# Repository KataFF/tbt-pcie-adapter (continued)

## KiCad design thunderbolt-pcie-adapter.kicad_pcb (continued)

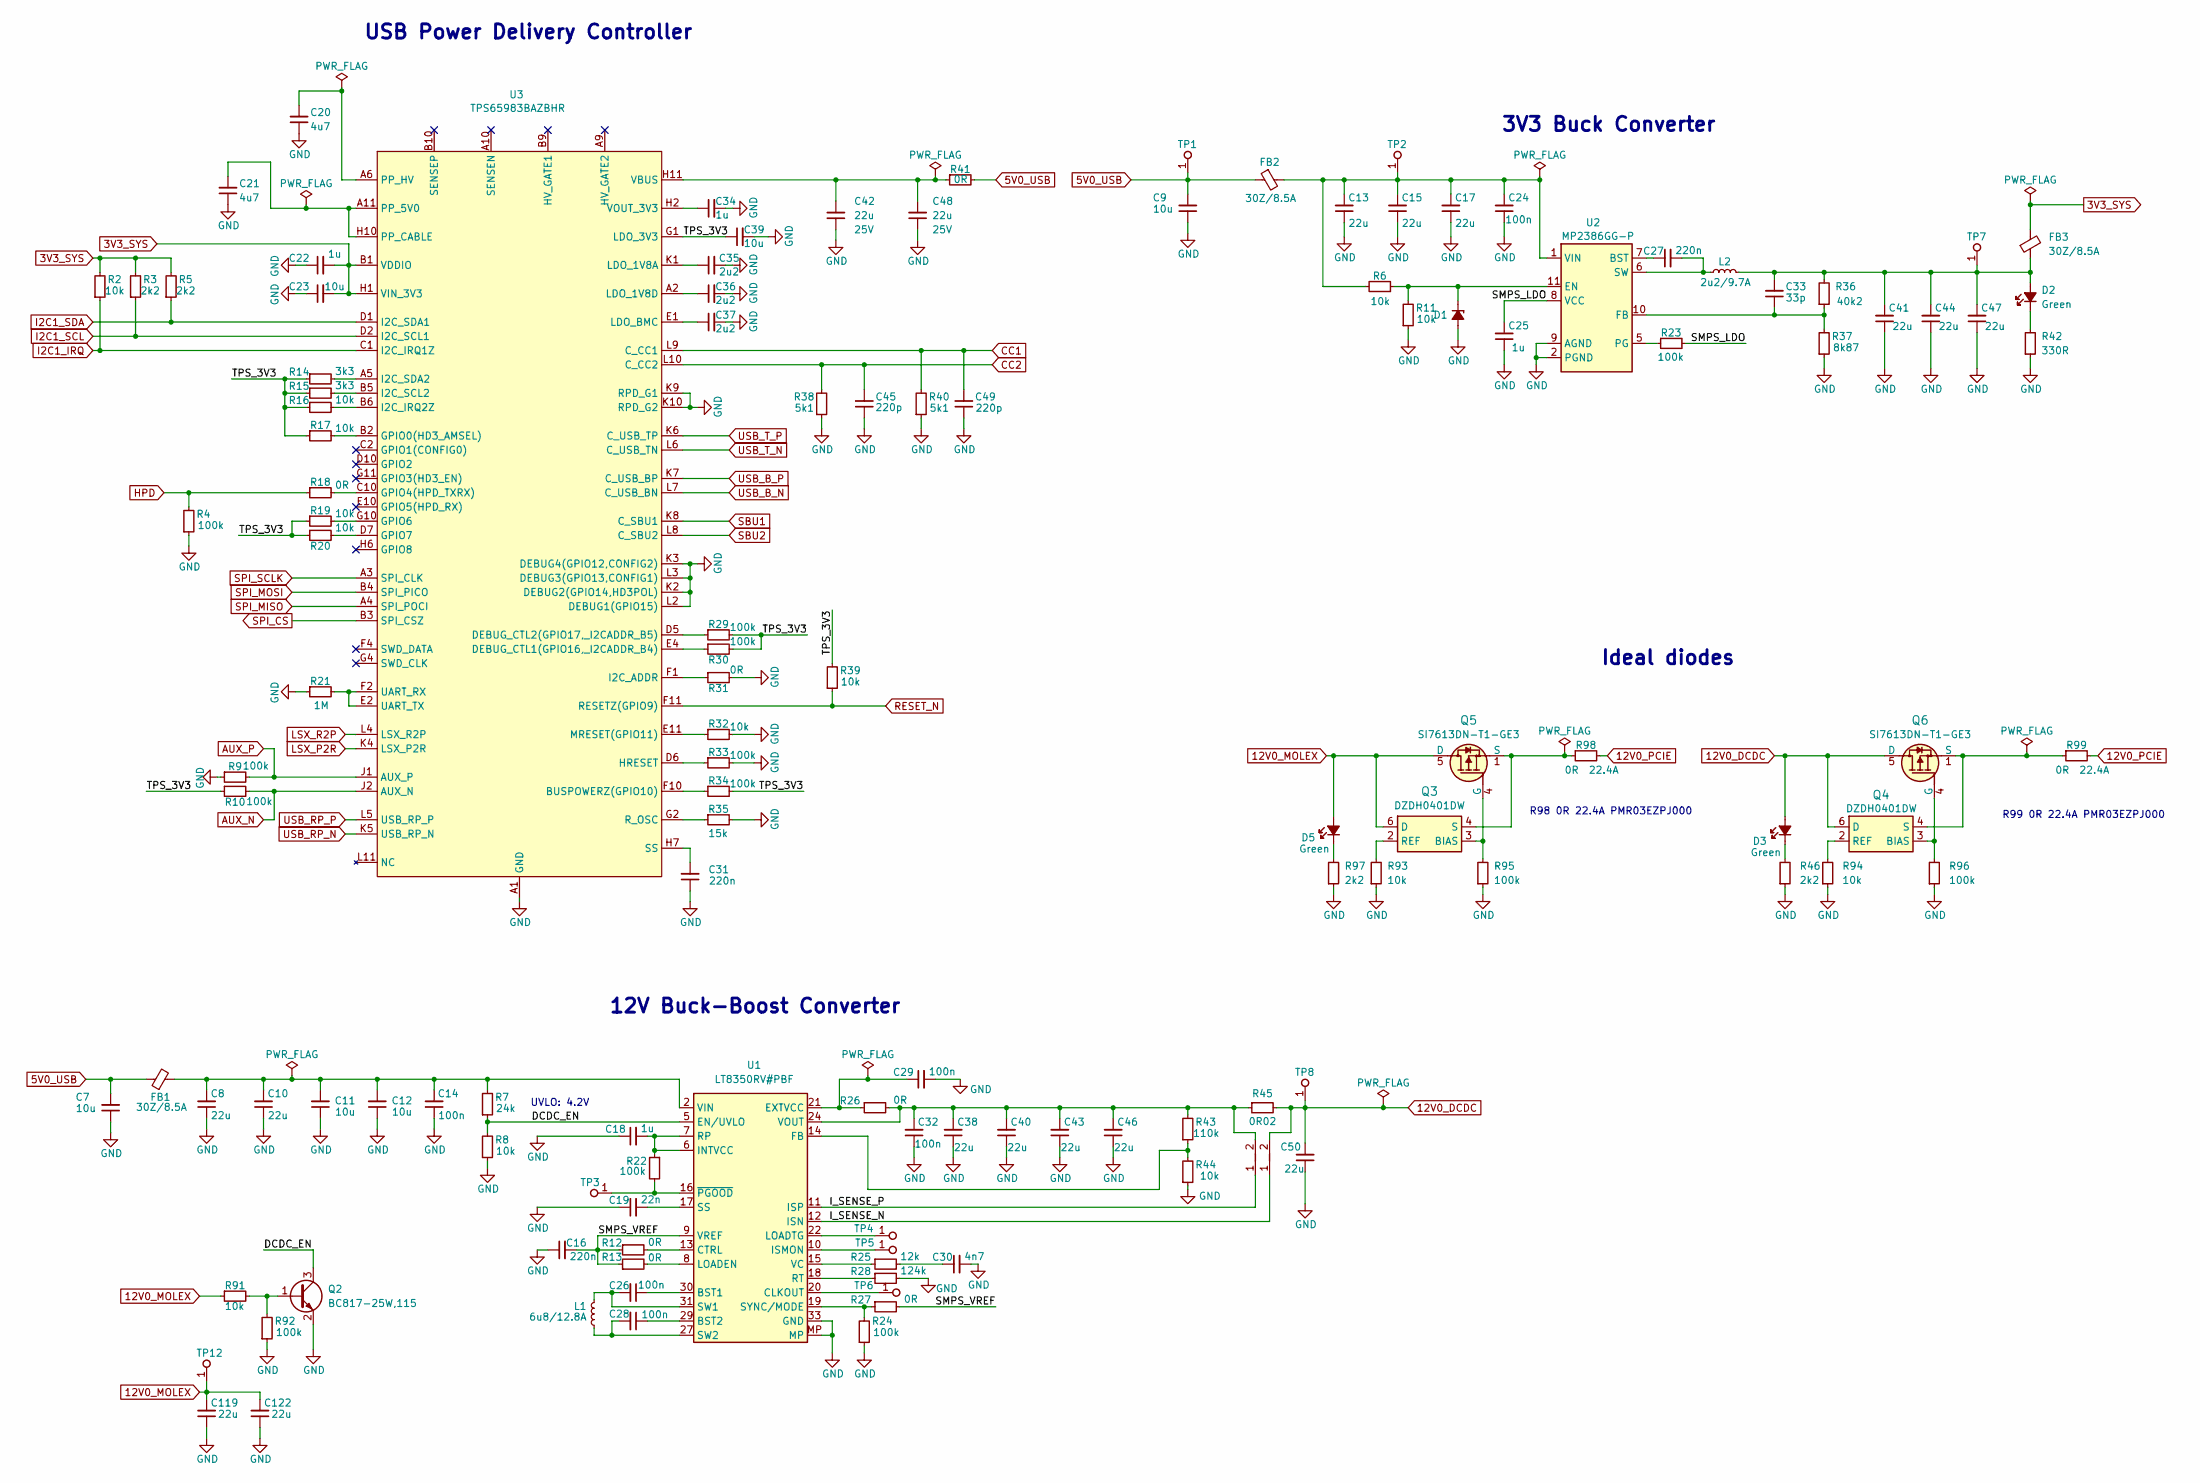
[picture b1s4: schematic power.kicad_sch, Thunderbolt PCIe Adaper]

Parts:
C7, C9, C11, C12: C_10u_0805_35V; C_0805_2012Metric; Voltage 35V; MPN GRM21BR6YA106KE43L
C8, C10, C13, C15, C17: C_22u_1206_35V; C_1206_3216Metric; Voltage 35V; MPN 3216X5R1V226M160AC
C14, C24, C26, C28, C29, C32: C_100n_0402; C_0402_1005Metric; Voltage 50V; MPN GRM155R61H104KE14D
C16, C27, C31: C_220n_0402; C_0402_1005Metric; MPN CC0402KRX5R6BB224
C18, C22, C25, C34: C_1u_0402; C_0402_1005Metric; MPN C1005X6S1A105K050BC
C19: C_22n_0402; C_0402_1005Metric; MPN GCM155R71H223MA55D
C20, C21: C_4u7_25V_0402; C_0402_1005Metric; Voltage 25V; MPN GRM155C61E475ME15J
C23, C39: C_10u_0402; C_0402_1005Metric; MPN CC0402MRX5R5BB106
C30: C_4n7_0402; C_0402_1005Metric; MPN CGA2B3X7S2A472K050BB
C33: C_33p_0402; C_0402_1005Metric; MPN 04025A330FAT2A
C35, C36, C37: C_2u2_0402; C_0402_1005Metric; MPN C1005X5R1A225K050BC
C38, C40, C43, C46, C50, C119, C122: C_22u_16V_0603; C_0603_1608Metric; Voltage 16V; MPN CL10A226MO7JZNC
C41, C44, C47: C_22u_0603; C_0603_1608Metric; MPN GRM188R60J226MEA0D
C42, C48: C_22u_25V_0805; C_0805_2012Metric; Voltage 25V; MPN CL21A226MAYNNNE
C45, C49: C_220p_0402; C_0402_1005Metric; MPN 04025C221JAT2A
D1: MM3Z3V3C; D_SOD-323F; MPN MM3Z3V3C
D2, D3, D5: LED_G_0603_KP-1608CGCK; LED_0603_1608Metric_G; MPN KP-1608CGCK
FB1, FB2, FB3: FB_30Z_8.5A_Murata-BLM21SN_0805; FB_0805_2012Metric; MPN BLM21SN300SZ1D
L1: L_6u8_12.8A_Coilcraft-XAL7070; L_Coilcraft-XAL7070; MPN XAL7070-682MEC
L2: L_2u2_9.7A_Coilcraft-XAL5030; L_Coilcraft-XAL5030; MPN XAL5030-222MEC
Q2: BC817-25W; SOT-323; MPN BC817-25W,115
Q3, Q4: DZDH0401DW; SOT-363; MPN DZDH0401DW
Q5, Q6: SI7613DN-T1-GE3; Vishay_PowerPAK_1212-8_Single; MPN SI7613DN-T1-GE3
R2, R6, R8, R11, R16, R17, R19, R20, R32, R39, R44, R91, R93, R94: R_10k_0402; R_0402_1005Metric; Tolerance 1%; MPN CR0402-FX-1002GLF
R3, R5, R46, R97: R_2k2_0402; R_0402_1005Metric; Tolerance 1%; MPN CR0402-FX-2201GLF
R4, R9, R10, R22, R23, R24, R29, R30, R33, R34, R92, R95, R96: R_100k_0402; R_0402_1005Metric; Tolerance 1%; MPN CR0402-FX-1003GLF
R7: R_24k_0402; R_0402_1005Metric; Tolerance 1%; MPN CR0402-FX-2402GLF
R12, R13, R18, R26, R27, R31: R_0R_0402; R_0402_1005Metric; MPN ERJ2GE0R00X
R14, R15: R_3k3_0402; R_0402_1005Metric; Tolerance 1%; MPN CR0402-FX-3301GLF
R21: R_1M_0402; R_0402_1005Metric; Tolerance 1%; MPN CR0402-FX-1004GLF
R25: R_12k_0402; R_0402_1005Metric; Tolerance 1%; MPN CR0402-FX-1202GLF
R28: R_124k_0402; R_0402_1005Metric; Tolerance 1%; MPN CR0402-FX-1243GLF
R35: R_15k_0.1%_0402; R_0402_1005Metric; Tolerance 0.1%; MPN ERA-2ARB153X
R36: R_40k2_0402; R_0402_1005Metric; Tolerance 1%; MPN CR0402-FX-4022GLF
R37: R_8k87_0402; R_0402_1005Metric; Tolerance 1%; MPN CR0402-FX-8871GLF
R38, R40: R_5k1_0402; R_0402_1005Metric; Tolerance 1%; MPN CR0402-FX-5101GLF
R41: R_0R_0603; R_0603_1608Metric; MPN CR0603-J/-000ELF
R42: R_330R_0402; R_0402_1005Metric; Tolerance 1%; MPN CR0402-FX-3300GLF
R43: R_110k_0402; R_0402_1005Metric; Tolerance 1%; MPN CR0402-FX-1103GLF
R45: R_0R02_1206; R_1206_3216Metric; Tolerance 1%; MPN WSLP1206R0200FEA
R98, R99: R_0R_22.4A_0603; R_0603_1608Metric; Tolerance template_tolerance; MPN PMR03EZPJ000
TP1, TP2, TP3, TP5, TP7, TP8, TP12: TP_1mm_SMD; TP_SMD_1mm
TP4, TP6: TP_0.75mm_SMD; TP_SMD_0.75mm
TP10, TP11: Net-Tie_P0.1mm; NetTie-2_SMD_Pad0.1mm
U1: LT8350RV; QFN-32-4EP_4x6mm_P0.5mm; MPN LT8350RV#PBF
U2: MP2386GG; QFN-11_2x2mm_P0.5mm; MPN MP2386GG-P
U3: TPS65983BAZBHR; IC_TPS65983BAZBHR; MPN TPS65983BAZBHR

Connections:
3V3_SYS: C22.2, C23.2, FB3.2, R2.2, R3.2, R5.2, U3.B1 (VDDIO), U3.H1 (VIN_3V3); also elsewhere on the board
5V0_USB: C7.2, C9.2, FB1.1, FB2.1, R41.2, TP1.1; also elsewhere on the board
12V0_DCDC: C50.2, D3.2 (A), Q4.6 (D), Q6.5 (D), R45.2, TP8.1, TP11.2
12V0_MOLEX: C119.2, C122.2, D5.2 (A), Q3.6 (D), Q5.5 (D), R91.1, TP12.1; also elsewhere on the board
12V0_PCIE: R98.2, R99.2; also elsewhere on the board
/Power/DCDC_EN: Q2.3 (C), R7.1, R8.2, U1.5 (EN/UVLO)
/Power/I_SENSE_N: TP11.1, U1.12 (ISN)
/Power/I_SENSE_P: TP10.1, U1.11 (ISP)
/Power/SMPS_LDO: C25.2, R23.2, U2.8 (VCC)
/Power/SMPS_VREF: C16.2, R12.1, R13.1, R27.2, U1.9 (VREF)
/Power/TPS_3V3: C39.1, R10.1, R14.1, R15.1, R16.1, R17.1, R19.1, R20.1, R29.2, R30.2, R34.2, R39.2, U3.G1 (LDO_3V3)
AUX_N: R10.2, U3.J2 (AUX_N); also elsewhere on the board
AUX_P: R9.2, U3.J1 (AUX_P); also elsewhere on the board
CC1: C49.2, R40.2, U3.L9 (C_CC1); also elsewhere on the board
CC2: C45.2, R38.2, U3.L10 (C_CC2); also elsewhere on the board
GND: C7.1, C8.1, C9.1, C10.1, C11.1, C12.1, C13.1, C14.1, C15.1, C16.1, C17.1, C18.1, C19.1, C20.1, C21.1, C22.1, C23.1, C24.1, C25.1, C29.2, C30.2, C31.1, C32.1, C34.2, C35.2, C36.2, C37.2, C38.1, C39.2, C40.1, C41.1, C42.1, C43.1, C44.1, C45.1, C46.1, C47.1, C48.1, C49.1, C50.1, C119.1, C122.1, D1.2 (A), Q2.2 (E), R4.1, R8.1, R9.1, R11.1, R21.1, R24.1, R28.2, R31.2, R32.2, R33.2, R35.2, R37.1, R38.1, R40.1, R42.1, R44.1, R46.1, R92.1, R93.1, R94.1, R95.1, R96.1, R97.1, U1.33 (GND), U1.34 (GND), U1.35 (GND), U1.36 (GND), U1.MP, U2.2 (PGND), U2.3 (PGND), U2.4 (PGND), U2.9 (AGND), U3.A1 (GND), U3.B8 (GND), U3.D8 (GND), U3.E5 (GND), U3.E6 (GND), U3.E7 (GND), U3.E8 (GND), U3.F5 (GND), U3.F6 (GND), U3.F7 (GND), U3.F8 (GND), U3.G5 (GND), U3.G6 (GND), U3.G7 (GND), U3.G8 (GND), U3.H4 (GND), U3.H5 (GND), U3.H8 (GND), U3.K2 (DEBUG2(GPIO14,HD3POL)), U3.K3 (DEBUG4(GPIO12,CONFIG2)), U3.K9 (RPD_G1), U3.K10 (RPD_G2), U3.L1 (GND), U3.L2 (DEBUG1(GPIO15)), U3.L3 (DEBUG3(GPIO13,CONFIG1)); also elsewhere on the board
HPD: R4.2, R18.1; also elsewhere on the board
I2C1_IRQ: R2.1, U3.C1 (I2C_IRQ1Z); also elsewhere on the board
I2C1_SCL: R3.1, U3.D2 (I2C_SCL1); also elsewhere on the board
I2C1_SDA: R5.1, U3.D1 (I2C_SDA1); also elsewhere on the board
LSX_P2R: U3.K4 (LSX_P2R); also elsewhere on the board
LSX_R2P: U3.L4 (LSX_R2P); also elsewhere on the board
unnamed: C8.2, C10.2, C11.2, C12.2, C14.2, FB1.2, R7.2, U1.2 (VIN), U1.3 (VIN)
unnamed: C26.2, L1.1, U1.31 (SW1), U1.32 (SW1)
unnamed: C28.2, L1.2, U1.27 (SW2), U1.28 (SW2)
unnamed: C30.1, R25.2
unnamed: C32.2, C38.2, C40.2, C43.2, C46.2, R26.2, R43.2, R45.1, TP10.2, U1.24 (VOUT), U1.25 (VOUT)
unnamed: D1.1 (C), R6.1, R11.2, U2.11 (EN)
unnamed: C33.2, C41.2, C44.2, C47.2, D2.2 (A), FB3.1, L2.2, R36.2, TP7.1
unnamed: D2.1 (C), R42.2
unnamed: D3.1 (C), R46.2
unnamed: D5.1 (C), R97.2
unnamed: Q2.1 (B), R91.2, R92.2
unnamed: Q3.3 (BIAS), Q5.4 (G), R95.2
unnamed: Q3.2 (REF), R93.2
unnamed: Q3.4 (S), Q5.1 (S), Q5.2 (S), Q5.3 (S), R98.1
unnamed: Q4.3 (BIAS), Q6.4 (G), R96.2
unnamed: Q4.2 (REF), R94.2
unnamed: Q4.4 (S), Q6.1 (S), Q6.2 (S), Q6.3 (S), R99.1
unnamed: C26.1, U1.30 (BST1)
unnamed: C28.1, U1.29 (BST2)
unnamed: TP6.1, U1.20 (CLKOUT)
unnamed: R12.2, U1.13 (CTRL)
unnamed: C29.1, R26.1, U1.21 (EXTVCC)
unnamed: R43.1, R44.2, U1.14 (FB)
unnamed: C18.2, R22.1, U1.6 (INTVCC), U1.7 (RP)
unnamed: TP5.1, U1.10 (ISMON)
unnamed: R13.2, U1.8 (LOADEN)
unnamed: TP4.1, U1.22 (LOADTG)
unnamed: R28.1, U1.18 (RT)
unnamed: C19.2, U1.17 (SS)
unnamed: R24.2, R27.1, U1.19 (SYNC/MODE)
unnamed: R25.1, U1.15 (VC)
unnamed: R22.2, TP3.1, U1.16 (~PGOOD)
unnamed: C27.1, U2.7 (BST)
unnamed: C33.1, R36.1, R37.2, U2.10 (FB)
unnamed: R23.1, U2.5 (PG)
unnamed: C27.2, L2.1, U2.6 (SW)
unnamed: C13.2, C15.2, C17.2, C24.2, FB2.2, R6.2, TP2.1, U2.1 (VIN)
unnamed: R34.1, U3.F10 (BUSPOWERZ(GPIO10))
unnamed: R30.1, U3.E4 (DEBUG_CTL1(GPIO16,_I2CADDR_B4))
unnamed: R29.1, U3.D5 (DEBUG_CTL2(GPIO17,_I2CADDR_B5))
unnamed: R17.2, U3.B2 (GPIO0(HD3_AMSEL))
unnamed: R18.2, U3.C10 (GPIO4(HPD_TXRX))
unnamed: R19.2, U3.G10 (GPIO6)
unnamed: R20.2, U3.D7 (GPIO7)
unnamed: R33.1, U3.D6 (HRESET)
unnamed: R31.1, U3.F1 (I2C_ADDR)
unnamed: R16.2, U3.B6 (I2C_IRQ2Z)
unnamed: R15.2, U3.B5 (I2C_SCL2)
unnamed: R14.2, U3.A5 (I2C_SDA2)
unnamed: C35.1, U3.K1 (LDO_1V8A)
unnamed: C36.1, U3.A2 (LDO_1V8D)
unnamed: C37.1, U3.E1 (LDO_BMC)
unnamed: R32.1, U3.E11 (MRESET(GPIO11))
unnamed: R35.1, U3.G2 (R_OSC)
unnamed: C31.2, U3.H7 (SS)
unnamed: R21.2, U3.E2 (UART_TX), U3.F2 (UART_RX)
unnamed: C34.1, U3.H2 (VOUT_3V3)
PP_5V0: C21.2, U3.A11 (PP_5V0), U3.B11 (PP_5V0), U3.C11 (PP_5V0), U3.D11 (PP_5V0), U3.H10 (PP_CABLE)
PP_HV: C20.2, U3.A6 (PP_HV), U3.A7 (PP_HV), U3.A8 (PP_HV), U3.B7 (PP_HV)
RESET_N: R39.1, U3.F11 (RESETZ(GPIO9)); also elsewhere on the board
SBU1: U3.K8 (C_SBU1); also elsewhere on the board
SBU2: U3.L8 (C_SBU2); also elsewhere on the board
SPI_CS: U3.B3 (SPI_CSZ); also elsewhere on the board
SPI_MISO: U3.A4 (SPI_POCI); also elsewhere on the board
SPI_MOSI: U3.B4 (SPI_PICO); also elsewhere on the board
SPI_SCLK: U3.A3 (SPI_CLK); also elsewhere on the board
USB_B_N: U3.L7 (C_USB_BN); also elsewhere on the board
USB_B_P: U3.K7 (C_USB_BP); also elsewhere on the board
USB_RP_N: U3.K5 (USB_RP_N); also elsewhere on the board
USB_RP_P: U3.L5 (USB_RP_P); also elsewhere on the board
USB_T_N: U3.L6 (C_USB_TN); also elsewhere on the board
USB_T_P: U3.K6 (C_USB_TP); also elsewhere on the board
VBUS: C42.2, C48.2, R41.1, U3.H11 (VBUS), U3.J10 (VBUS), U3.J11 (VBUS), U3.K11 (VBUS)

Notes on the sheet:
UVLO: 4.2V
R99 0R 22.4A PMR03EZPJ000
Ideal diodes
USB Power Delivery Controller
12V Buck-Boost Converter
3V3 Buck Converter
R98 0R 22.4A PMR03EZPJ000

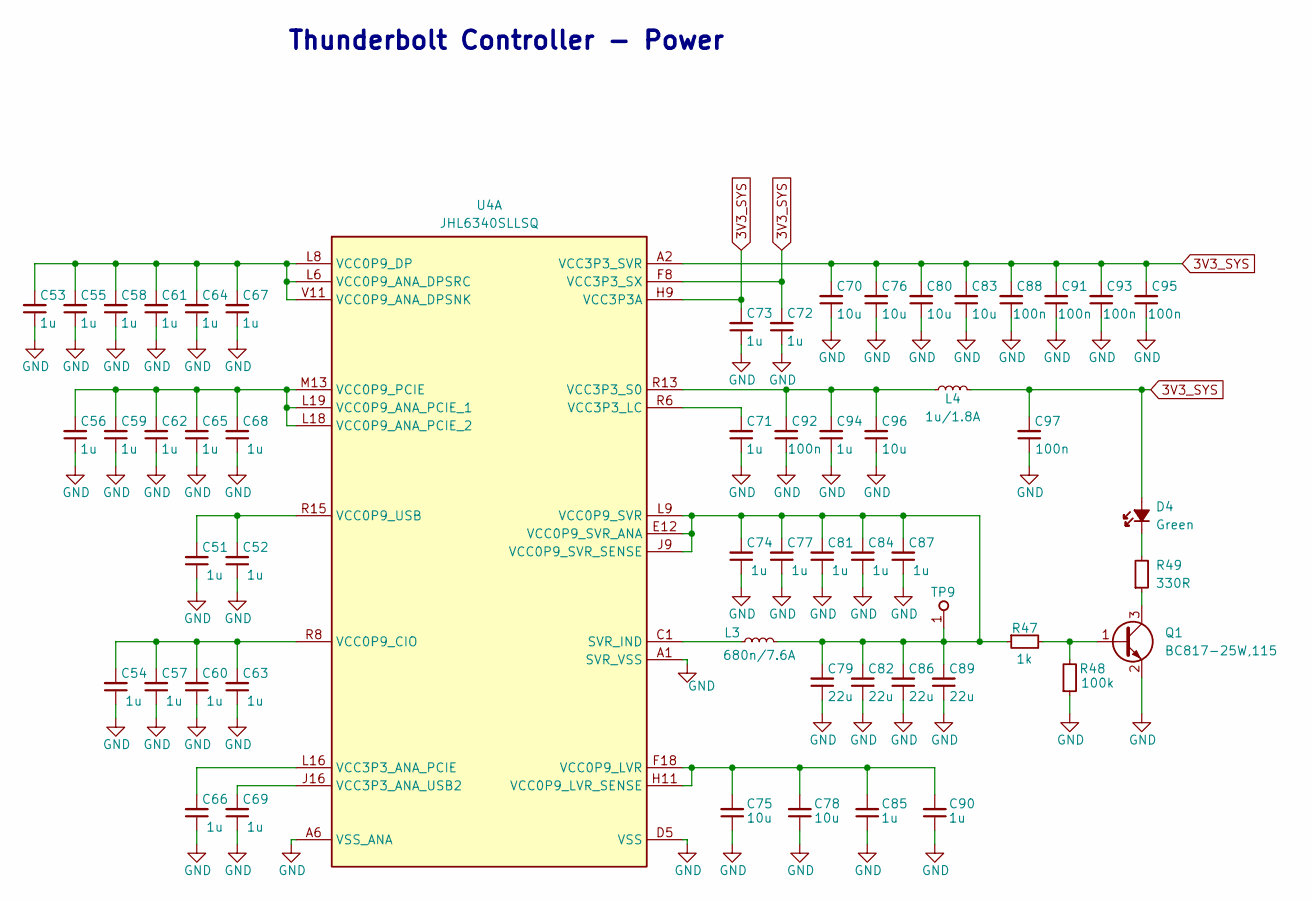
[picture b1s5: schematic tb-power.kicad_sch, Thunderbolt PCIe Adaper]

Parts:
C51, C52, C53, C54, C55, C56, C57, C58, C59, C60, C61, C62, C63, C64, C65, C66, C67, C68, C69, C71, C72, C73, C74, C77, C81, C84, C85, C87, C90, C94: C_1u_0402; C_0402_1005Metric; MPN C1005X6S1A105K050BC
C70, C75, C76, C78, C80, C83, C96: C_10u_0402; C_0402_1005Metric; MPN CC0402MRX5R5BB106
C79, C82, C86, C89: C_22u_0603; C_0603_1608Metric; MPN GRM188R60J226MEA0D
C88, C91, C92, C93, C95, C97: C_100n_0402; C_0402_1005Metric; Voltage 50V; MPN GRM155R61H104KE14D
D4: LED_G_0603_KP-1608CGCK; LED_0603_1608Metric_G; MPN KP-1608CGCK
L3: L_680n_7.6A_IHLP1616BZ; L_Vishay-IHLP1616BZ; MPN IHLP1616BZERR68M5A
L4: L_1u_1.8A_0603; L_0603_1608Metric; MPN DFE18SBN1R0ME0L
Q1: BC817-25W; SOT-323; MPN BC817-25W,115
R47: R_1k_0402; R_0402_1005Metric; Tolerance 1%; MPN CR0402-FX-1001GLF
R48: R_100k_0402; R_0402_1005Metric; Tolerance 1%; MPN CR0402-FX-1003GLF
R49: R_330R_0402; R_0402_1005Metric; Tolerance 1%; MPN CR0402-FX-3300GLF
TP9: TP_1mm_SMD; TP_SMD_1mm
U4: JHL6340SLLSQ; MPN JHL6340SLLSQ

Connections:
3V3_SYS: C70.2, C72.2, C73.2, C76.2, C80.2, C83.2, C88.2, C91.2, C93.2, C95.2, C97.2, D4.2 (A), L4.2, U4.A2 (VCC3P3_SVR), U4.A3 (VCC3P3_SVR), U4.B3 (VCC3P3_SVR), U4.F8 (VCC3P3_SX), U4.H9 (VCC3P3A); also elsewhere on the board
GND: C51.1, C52.1, C53.1, C54.1, C55.1, C56.1, C57.1, C58.1, C59.1, C60.1, C61.1, C62.1, C63.1, C64.1, C65.1, C66.1, C67.1, C68.1, C69.1, C70.1, C71.1, C72.1, C73.1, C74.1, C75.1, C76.1, C77.1, C78.1, C79.1, C80.1, C81.1, C82.1, C83.1, C84.1, C85.1, C86.1, C87.1, C88.1, C89.1, C90.1, C91.1, C92.1, C93.1, C94.1, C95.1, C96.1, C97.1, Q1.2 (E), R48.1, U4.A1 (SVR_VSS), U4.A6 (VSS_ANA), U4.A8 (VSS_ANA), U4.A10 (VSS_ANA), U4.A12 (VSS_ANA), U4.A14 (VSS_ANA), U4.A16 (VSS_ANA), U4.A18 (VSS_ANA), U4.A20 (VSS_ANA), U4.A22 (VSS_ANA), U4.AA22 (VSS_ANA), U4.AA23 (VSS_ANA), U4.AB1 (VSS), U4.AB6 (VSS_ANA), U4.AB8 (VSS_ANA), U4.AB10 (VSS_ANA), U4.AB12 (VSS_ANA), U4.AB14 (VSS_ANA), U4.AB16 (VSS_ANA), U4.AB18 (VSS_ANA), U4.AB20 (VSS_ANA), U4.AB22 (VSS_ANA), U4.AC2 (VSS), U4.AC6 (VSS_ANA), U4.AC8 (VSS_ANA), U4.AC10 (VSS_ANA), U4.AC12 (VSS_ANA), U4.AC14 (VSS_ANA), U4.AC16 (VSS_ANA), U4.AC18 (VSS_ANA), U4.AC20 (VSS_ANA), U4.AC22 (VSS_ANA), U4.B1 (SVR_VSS), U4.B2 (SVR_VSS), U4.B6 (VSS_ANA), U4.B8 (VSS_ANA), U4.B10 (VSS_ANA), U4.B12 (VSS_ANA), U4.B14 (VSS_ANA), U4.B16 (VSS_ANA), U4.B18 (VSS_ANA), U4.B20 (VSS_ANA), U4.B22 (VSS_ANA), U4.D5 (VSS), U4.D8 (VSS_ANA), U4.D9 (VSS_ANA), U4.D11 (VSS_ANA), U4.D12 (VSS_ANA), U4.D13 (VSS_ANA), U4.D15 (VSS_ANA), U4.D16 (VSS_ANA), U4.D18 (VSS_ANA), U4.E4 (VSS), U4.E5 (VSS), U4.E6 (VSS), U4.E8 (VSS_ANA), U4.E9 (VSS_ANA), U4.E11 (VSS_ANA), U4.E15 (VSS_ANA), U4.E16 (VSS_ANA), U4.E22 (VSS_ANA), U4.E23 (VSS_ANA), U4.F5 (VSS), U4.F6 (VSS), U4.F9 (VSS_ANA), U4.F16 (VSS_ANA), U4.F20 (VSS_ANA), U4.G22 (VSS_ANA), U4.G23 (VSS_ANA), U4.H1 (VSS_ANA), U4.H2 (VSS_ANA), U4.H5 (VSS), U4.H8 (VSS), U4.H12 (VSS_ANA), U4.H13 (VSS_ANA), U4.H15 (VSS_ANA), U4.H16 (VSS_ANA), U4.H20 (VSS_ANA), U4.J5 (VSS_ANA), U4.J8 (VSS), U4.J12 (VSS), U4.J13 (VSS), U4.J15 (VSS), U4.J18 (VSS_ANA), U4.J19 (VSS_ANA), U4.J20 (VSS_ANA), U4.J22 (VSS_ANA), U4.J23 (VSS_ANA), U4.K1 (VSS_ANA), U4.K2 (VSS_ANA), U4.L5 (VSS_ANA), U4.L13 (VSS), U4.L20 (VSS_ANA), U4.L22 (VSS_ANA), U4.L23 (VSS_ANA), U4.M1 (VSS_ANA), U4.M2 (VSS_ANA), U4.M5 (VSS_ANA), U4.M11 (VSS), U4.M12 (VSS), U4.M19 (VSS_ANA), U4.M20 (VSS_ANA), U4.N5 (VSS_ANA), U4.N8 (VSS), U4.N9 (VSS), U4.N11 (VSS), U4.N12 (VSS), U4.N13 (VSS), U4.N20 (VSS_ANA), U4.N22 (VSS_ANA), U4.N23 (VSS_ANA), U4.P1 (VSS_ANA), U4.P2 (VSS_ANA), U4.R5 (VSS_ANA), U4.R18 (VSS_ANA), U4.R19 (VSS_ANA), U4.R20 (VSS_ANA), U4.R22 (VSS_ANA), U4.R23 (VSS_ANA), U4.T1 (VSS_ANA), U4.T2 (VSS_ANA), U4.T5 (VSS_ANA), U4.T6 (VSS), U4.T8 (VSS), U4.T9 (VSS), U4.T13 (VSS), U4.T15 (VSS), U4.T16 (VSS), U4.T18 (VSS), U4.T20 (VSS_ANA), U4.U22 (VSS_ANA), U4.U23 (VSS_ANA), U4.V5 (VSS_ANA), U4.V6 (VSS_ANA), U4.V8 (VSS_ANA), U4.V9 (VSS_ANA), U4.V15 (VSS_ANA), U4.V16 (VSS_ANA), U4.V20 (VSS_ANA), U4.W5 (VSS_ANA), U4.W6 (VSS_ANA), U4.W8 (VSS_ANA), U4.W9 (VSS_ANA), U4.W20 (VSS_ANA), U4.W22 (VSS_ANA), U4.W23 (VSS_ANA), U4.Y9 (VSS_ANA), U4.Y13 (VSS_ANA), U4.Y20 (VSS_ANA); also elsewhere on the board
unnamed: D4.1 (C), R49.2
unnamed: L3.1, U4.C1 (SVR_IND), U4.C2 (SVR_IND), U4.D1 (SVR_IND)
unnamed: Q1.1 (B), R47.2, R48.2
unnamed: Q1.3 (C), R49.1
unnamed: C66.2, U4.L16 (VCC3P3_ANA_PCIE)
unnamed: C69.2, U4.J16 (VCC3P3_ANA_USB2)
unnamed: C71.2, U4.R6 (VCC3P3_LC)
unnamed: C92.2, C94.2, C96.2, L4.1, U4.R13 (VCC3P3_S0)
VCC0P9_ANA_DPSNK: C53.2, C55.2, C58.2, C61.2, C64.2, C67.2, U4.L6 (VCC0P9_ANA_DPSRC), U4.L8 (VCC0P9_DP), U4.L11 (VCC0P9_DP), U4.L12 (VCC0P9_DP), U4.M6 (VCC0P9_ANA_DPSRC), U4.M8 (VCC0P9_DP), U4.T11 (VCC0P9_DP), U4.T12 (VCC0P9_DP), U4.V11 (VCC0P9_ANA_DPSNK), U4.V12 (VCC0P9_ANA_DPSNK), U4.V13 (VCC0P9_ANA_DPSNK)
VCC0P9_ANA_PCIE_1: C56.2, C59.2, C62.2, C65.2, C68.2, U4.L18 (VCC0P9_ANA_PCIE_2), U4.L19 (VCC0P9_ANA_PCIE_1), U4.M13 (VCC0P9_PCIE), U4.M15 (VCC0P9_PCIE), U4.M16 (VCC0P9_PCIE), U4.M18 (VCC0P9_ANA_PCIE_2), U4.N18 (VCC0P9_ANA_PCIE_2), U4.N19 (VCC0P9_ANA_PCIE_1)
VCC0P9_CIO: C54.2, C57.2, C60.2, C63.2, U4.R8 (VCC0P9_CIO), U4.R9 (VCC0P9_CIO), U4.R11 (VCC0P9_CIO), U4.R12 (VCC0P9_CIO)
VCC0P9_LVR: C75.2, C78.2, C85.2, C90.2, U4.F18 (VCC0P9_LVR), U4.H11 (VCC0P9_LVR_SENSE), U4.H18 (VCC0P9_LVR), U4.J11 (VCC0P9_LVR)
VCC0P9_SVR: C74.2, C77.2, C79.2, C81.2, C82.2, C84.2, C86.2, C87.2, C89.2, L3.2, R47.1, TP9.1, U4.E12 (VCC0P9_SVR_ANA), U4.E13 (VCC0P9_SVR_ANA), U4.F11 (VCC0P9_SVR_ANA), U4.F12 (VCC0P9_SVR_ANA), U4.F13 (VCC0P9_SVR_ANA), U4.F15 (VCC0P9_SVR_ANA), U4.J9 (VCC0P9_SVR_SENSE), U4.L9 (VCC0P9_SVR), U4.M9 (VCC0P9_SVR)
VCC0P9_USB: C51.2, C52.2, U4.R15 (VCC0P9_USB), U4.R16 (VCC0P9_USB)

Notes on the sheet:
Thunderbolt Controller - Power

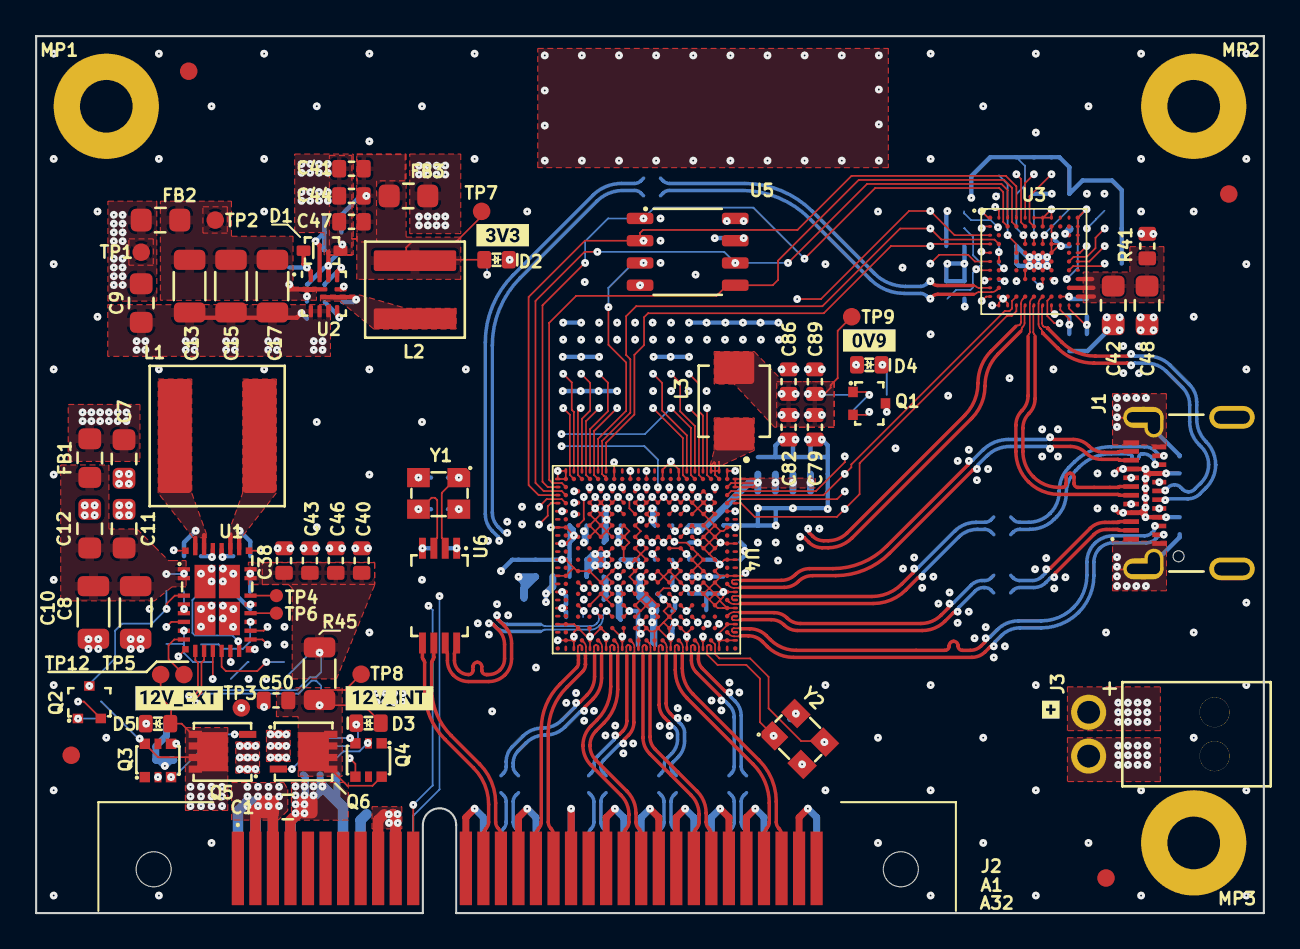
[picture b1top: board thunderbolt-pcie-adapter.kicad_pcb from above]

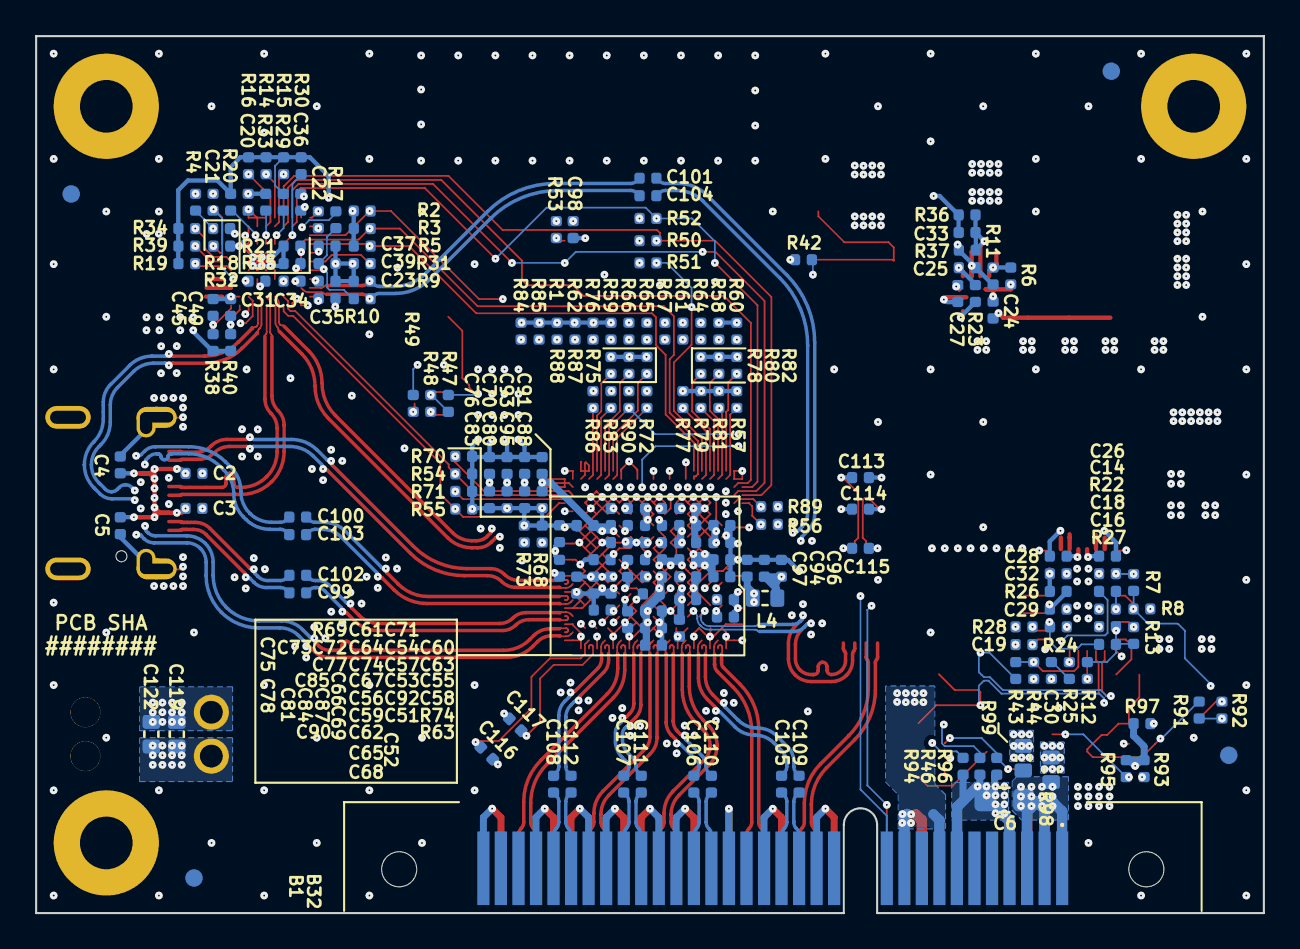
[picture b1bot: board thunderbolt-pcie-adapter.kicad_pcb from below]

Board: 6 copper layers, 70.0 x 50.0 mm, 276 parts (199 on the bottom side), 194 nets.

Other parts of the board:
kibuzzard-6453B5A4: G***; kibuzzard-6453B5A4
kibuzzard-6453B5AB: G***; kibuzzard-6453B5AB
kibuzzard-6453B7B3: G***; kibuzzard-6453B7B3
kibuzzard-6453B7B9: G***; kibuzzard-6453B7B9
kibuzzard-6453BA6B: G***; kibuzzard-6453BA6B

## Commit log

2025-05-08 Update project files to KiCad 8.0.6.
2025-05-08 Update README, clarify contributions
2025-05-09 PCB: N1 board name & rev text: Enlarge to facilitate manufacturabilty, update REV and DATE
2025-05-09 Update revision to 1.0.3.
2025-05-09 Bring back DRC exclusions from PCB to PROject file
2025-05-21 PCB: Update stackup params to PCBWay 6-layer w/ 1oz outer & 0.5oz inner layers.
    Values were taken from EQ2 as well as the following datasheets:
    https://www.pcbway.com/blog/PCB_Basic_Information/S1000H_Shengyi_Conventional_FR_4_Rigid_PCB_Materials.html
    https://www.chinapcbone.com/images/pdf/S1000H.pdf
    I assumed the original design is based on values for "FR4 Improved" material:
    https://www.eurocircuits.com/downloads/#BaseMaterials
2025-05-21 Set finish to ENIG as agreed with production
2025-05-22 Proj constr.: Increase min text thickness to 8 mils, add viewport for diff pair inspection
2025-05-22 Adjust logo text, add KxW signature
2025-05-22 Update default diff pair width & spacing for USB4&2 to PCBWay stackup external layers
2025-05-22 Lock JHL6340 fanout traces for DP adjustment
2025-05-22 Add predef sizes
2025-05-22 PCB: Reroute TB_RX1
2025-07-03 Measurement PCB: Add Kapton tape mask pieces for orientation on BGA footprint
    These are the two main Kapton tape mask pieces used for soldering 0402 terminating resistors on PCIe_RX3 DPs.
    I put them to make it easier to find the right pad on the footprint, among 300+ other ones.
2025-07-03 PCB: Generate and add Interactive HTML BOM + project config settings
2025-07-04 SCH: Fix typo in Title Block, clarify authorship
2025-07-05 Bring back the block diagram from history, make a paper-friendly variant with GIMP
